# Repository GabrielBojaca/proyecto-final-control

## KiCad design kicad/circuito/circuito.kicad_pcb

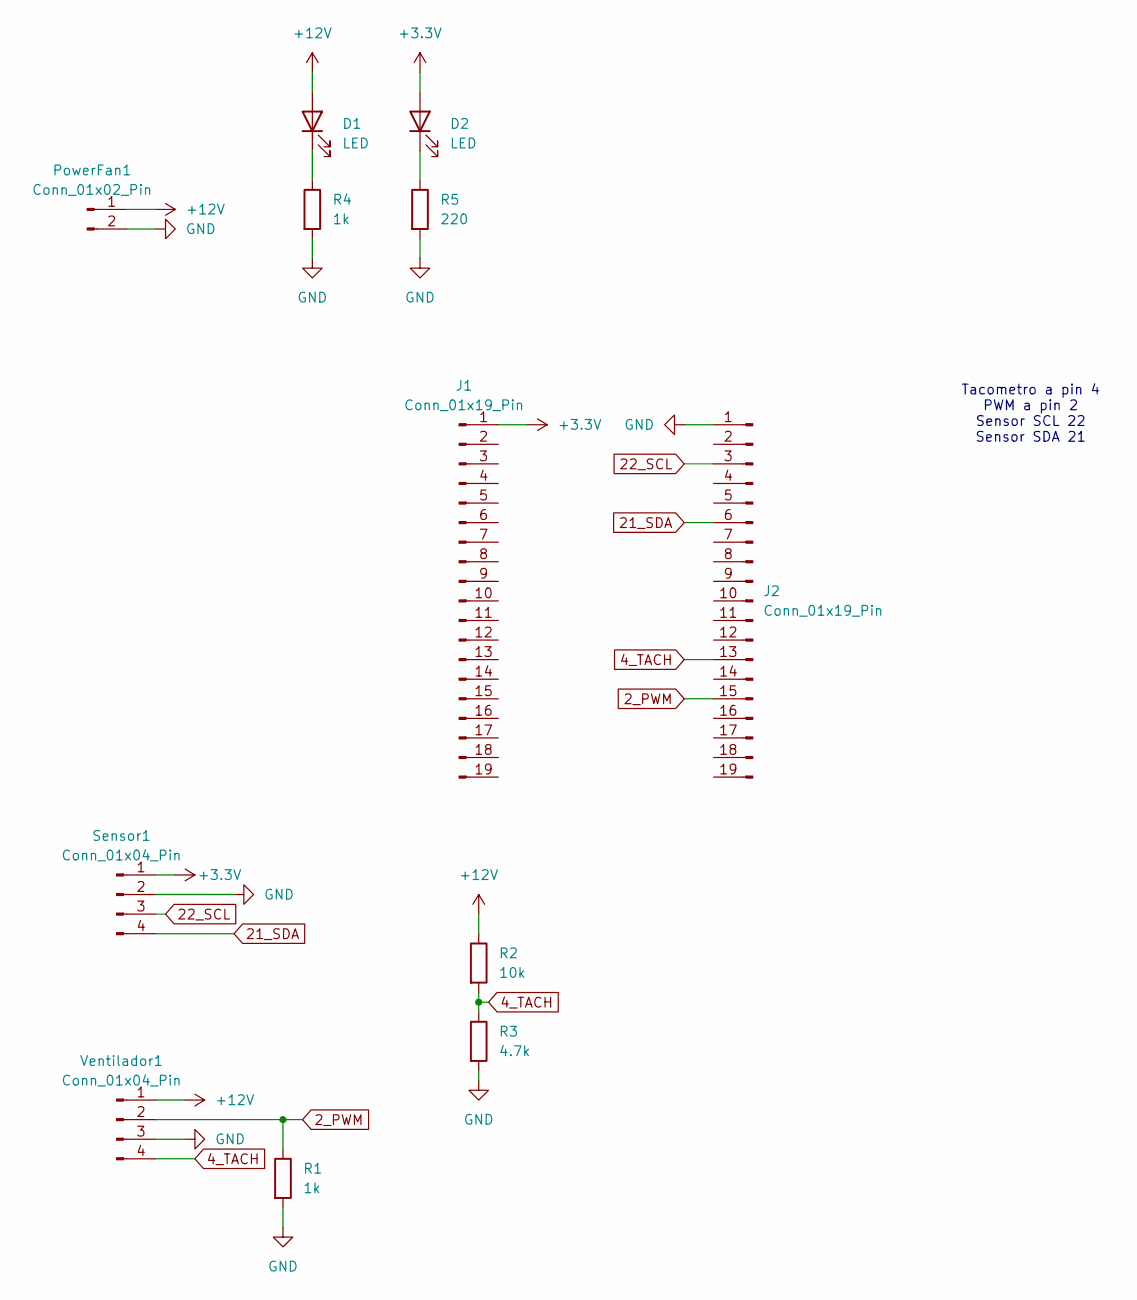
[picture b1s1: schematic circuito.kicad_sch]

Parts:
D1, D2: LED; LED_D5.0mm
J1, J2: Conn_01x19_Pin; PinHeader_1x19_P2.54mm_Vertical
PowerFan1: Conn_01x02_Pin; Molex_KK-254_AE-6410-04A_1x04_P2.54mm_Vertical
R1, R4: 1k; R_Axial_DIN0207_L6.3mm_D2.5mm_P7.62mm_Horizontal
R2: 10k; R_Axial_DIN0207_L6.3mm_D2.5mm_P7.62mm_Horizontal
R3: 4.7k; R_Axial_DIN0207_L6.3mm_D2.5mm_P7.62mm_Horizontal
R5: 220; R_Axial_DIN0207_L6.3mm_D2.5mm_P7.62mm_Horizontal
Sensor1: Conn_01x04_Pin; Molex_KK-254_AE-6410-04A_1x04_P2.54mm_Vertical
Ventilador1: Conn_01x04_Pin; Molex_KK-254_AE-6410-04A_1x04_P2.54mm_Vertical

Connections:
2_PWM: J2.15, R1.1, Ventilador1.2
4_TACH: J2.13, R2.2, R3.1, Ventilador1.4
21_SDA: J2.6, Sensor1.4
22_SCL: J2.3, Sensor1.3
+3.3V: D2.2 (A), J1.1, Sensor1.1
+12V: D1.2 (A), PowerFan1.1, R2.1, Ventilador1.1
GND: J2.1, PowerFan1.2, R1.2, R3.2, R4.2, R5.2, Sensor1.2, Ventilador1.3
unnamed: D1.1 (K), R4.1
unnamed: D2.1 (K), R5.1

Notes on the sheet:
Tacometro a pin 4 PWM a pin 2 Sensor SCL 22 Sensor SDA 21

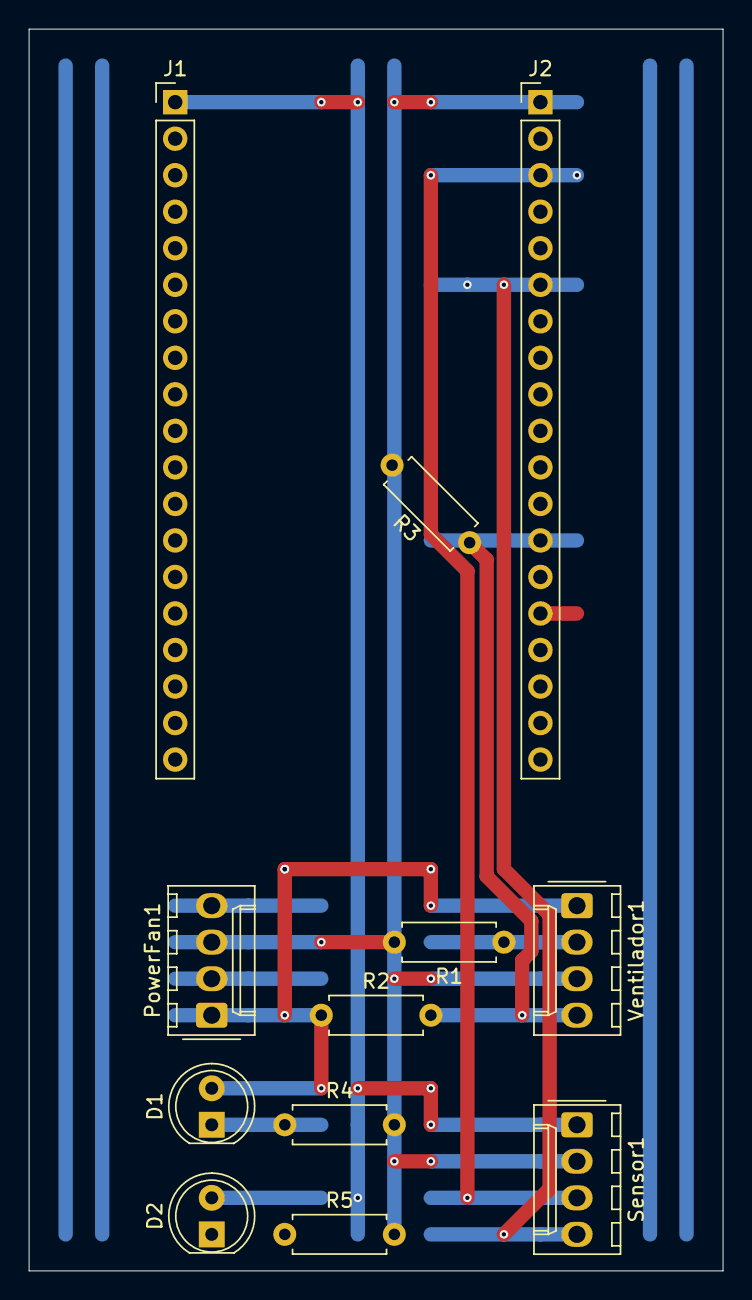
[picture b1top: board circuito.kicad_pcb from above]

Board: 2 copper layers, 48.3 x 86.4 mm, 12 parts (0 on the bottom side), 9 nets.

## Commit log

2025-02-24 Libreria de sensor de distancia agregada.
2025-02-24 entorno caracterizacion agregado junto con ejemplo de medicion de distancia en denky32
2025-02-25 Implementacion kp para caracterización y relevo de Astrom
2025-02-25 Lectura de puerto serie 240s
2025-02-25 Correción envs platformio.io
2025-02-26 Estimación Ku Omega
2025-02-27 agregados archivos PCB
2025-02-27 Corrección ueq con base alta
2025-02-27 Actualización datos tomados para caracterización
2025-03-02 Implementación preliminar control PID con referencia por puerto serial.
2025-03-02 Correción envs platformio.ini
2025-03-04 correción parametros PID y caracterización
2025-03-04 Actualización 3 sistemas PID
2025-03-04 Agregados archivos MATLAB
2025-07-25 Creado con Colab
